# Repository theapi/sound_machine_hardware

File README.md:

# Sound Machine Hardware

Hardware for https://github.com/theapi/sound_machine using Kicad

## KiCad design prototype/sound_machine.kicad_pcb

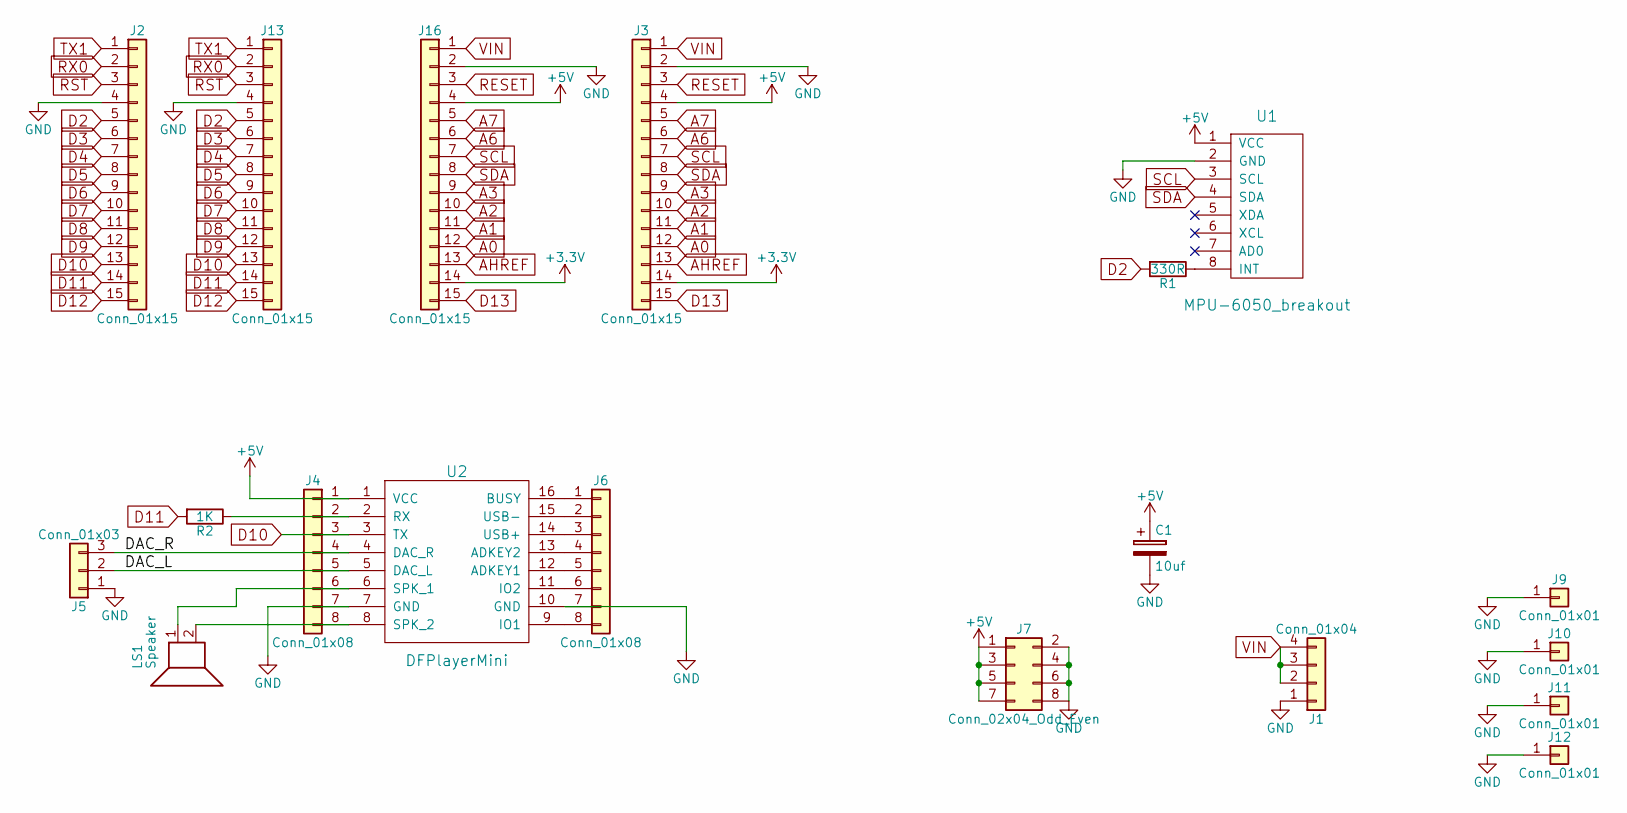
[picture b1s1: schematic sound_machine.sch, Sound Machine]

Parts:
C1: 10uf; CP_Radial_D5.0mm_P2.50mm
J1: Conn_01x04; Socket_Strip_Straight_1x04
J2, J3: Conn_01x15; Pin_Header_Straight_1x15_Pitch2.54mm
J4, J6: Conn_01x08; Pin_Header_Straight_1x08_Pitch2.54mm
J5: Conn_01x03; Pin_Header_Straight_1x03_Pitch2.54mm
J7: Conn_02x04_Odd_Even; Pin_Header_Straight_2x04_Pitch2.54mm
J9, J10, J11, J12: Conn_01x01; MountingHole_3.2mm_M3_DIN965_Pad
J13, J16: Conn_01x15; Socket_Strip_Straight_1x15_Pitch2.54mm
LS1: Speaker; Pin_Header_Straight_1x02_Pitch2.54mm
R1: 330R; R_Axial_DIN0207_L6.3mm_D2.5mm_P10.16mm_Horizontal
R2: 1K; R_0805_HandSoldering
U1: MPU-6050_breakout; MPU-6050
U2: DFPlayerMini

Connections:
+3V3: J3.14, J16.14
+5V: C1.1, J3.4, J4.1, J7.1, J7.3, J7.5, J7.7, J16.4, U1.1 (VCC), U2.1 (VCC)
/DAC_L: J4.5, J5.2, U2.5 (DAC_L)
/DAC_R: J4.4, J5.3, U2.4 (DAC_R)
A0: J3.12, J16.12
A1: J3.11, J16.11
A2: J3.10, J16.10
A3: J3.9, J16.9
A6: J3.6, J16.6
A7: J3.5, J16.5
AHREF: J3.13, J16.13
D2: J2.5, J13.5, R1.2
D3: J2.6, J13.6
D4: J2.7, J13.7
D5: J2.8, J13.8
D6: J2.9, J13.9
D7: J2.10, J13.10
D8: J2.11, J13.11
D9: J2.12, J13.12
D10: J2.13, J4.3, J13.13, U2.3 (TX)
D11: J2.14, J13.14, R2.2
D12: J2.15, J13.15
D13: J3.15, J16.15
GND: C1.2, J1.1, J2.4, J3.2, J4.7, J5.1, J6.7, J7.2, J7.4, J7.6, J7.8, J9.1, J10.1, J11.1, J12.1, J13.4, J16.2, U1.2 (GND), U2.7 (GND), U2.10 (GND)
unnamed: J4.2, R2.1, U2.2 (RX)
unnamed: J4.6, LS1.1, U2.6 (SPK_1)
unnamed: J4.8, LS1.2, U2.8 (SPK_2)
unnamed: J6.1, U2.16 (BUSY)
unnamed: J6.2, U2.15 (USB-)
unnamed: J6.3, U2.14 (USB+)
unnamed: J6.4, U2.13 (ADKEY2)
unnamed: J6.5, U2.12 (ADKEY1)
unnamed: J6.6, U2.11 (IO2)
unnamed: J6.8, U2.9 (IO1)
unnamed: R1.1, U1.8 (INT)
RESET: J3.3, J16.3
RST: J2.3, J13.3
RX0: J2.2, J13.2
SCL: J3.7, J16.7, U1.3 (SCL)
SDA: J3.8, J16.8, U1.4 (SDA)
TX1: J2.1, J13.1
VIN: J1.2, J1.3, J1.4, J3.1, J16.1

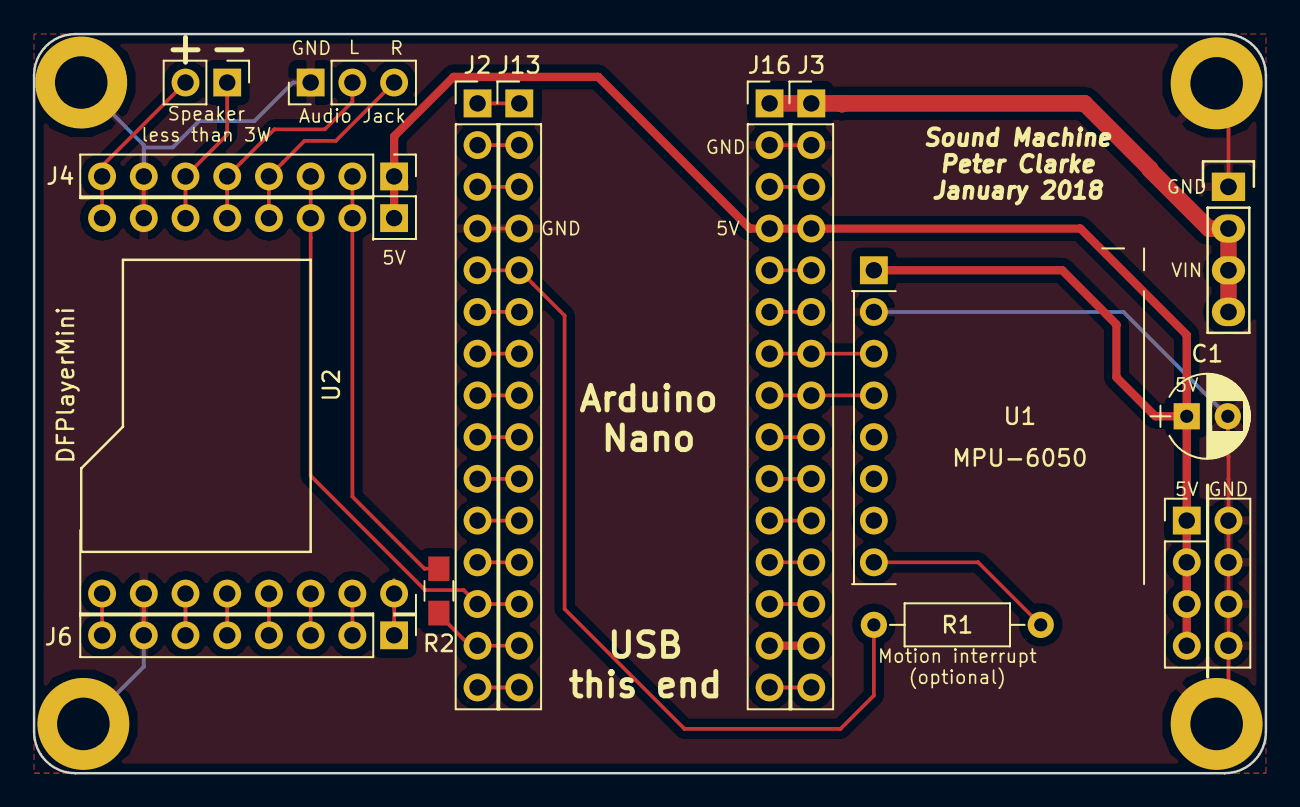
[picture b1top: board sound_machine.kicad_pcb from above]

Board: 2 copper layers, 75.0 x 45.0 mm, 19 parts (0 on the bottom side), 42 nets.

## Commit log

2017-12-26 Harware
2017-12-26 Prototype
2017-12-26 Gerbers
2017-12-26 Plot for www.seeedstudio.com
2017-12-26 Render
2017-12-26 Corrected drill file (Seeed docs wrong about using millimeters)
2017-12-27 Removed jack
2017-12-27 Rounded corners
2017-12-27 Capacitor
2017-12-27 Layout change
2019-10-26 Schematic
